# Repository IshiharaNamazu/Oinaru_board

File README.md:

# Oinaru Board

Oinaru Boardは、USB Type-Cからセンサへ電源を供給しながら、PCとセンサ間のUSB–RS485通信を行うための変換基板です。

USB Type-Cから入力された電圧は、XC9306昇降圧DC-DCコンバータモジュールで5 Vに安定化してセンサへ供給します。

USB–UART変換にはCH340E、差動信号の送受信には2個のMAX485Eを使用し、TX±／RX±による4線式通信に対応しています。

## 特長

- USB Type-C（USB 2.0）接続
- センサへの5 V電源供給
- XC9306モジュールによるUSB入力電圧の昇降圧・安定化
- USB–RS485変換
- TX±／RX±の4線式全二重通信
- USB接続および5 V電源のLED表示
- 通信線の終端抵抗を実装可能

## 基板外観

### 表面

### 裏面

## センサ側コネクタ（XH）

| ピン | 信号 |
| ---: | :--- |
| 1 | GND |
| 2 | +5 V |
| 3 | TX+ |
| 4 | TX- |
| 5 | RX+ |
| 6 | RX- |

ピン番号はKiCadの回路図・基板データ上の番号です。実際に接続する前に、使用するセンサの仕様書と信号方向・ピン配列を照合してください。
基盤のTXはセンサのRXと接続されることに注意してください

## 使用方法

1. XHコネクタにセンサを接続します。
2. Oinaru BoardとPCをUSB Type-Cケーブルで接続します。
3. PCに認識されたCH340Eのシリアルポートを、使用するソフトウェアから開きます。
4. センサの仕様に合わせて通信速度などを設定し、通信を開始します。

## 主な構成部品

| 部品 | 用途 |
| :--- | :--- |
| CH340E | USB–UART変換 |
| MAX485E × 2 | TX／RX差動信号変換 |
| XC9306昇降圧モジュール | USB入力電圧を5 Vに安定化 |
| USB Type-Cレセプタクル | PC接続・電源入力 |
| 6ピンコネクタ | センサ接続 |

## オプション部品

以下の部品は必要に応じて実装するオプションです。

- `TRIM_R`：XC9306モジュールの出力電圧調整用抵抗です。使用するモジュールの仕様と必要な出力電圧に合わせて抵抗値を選定します。
- `R6`：TX差動信号線の終端抵抗です。必要に応じて実装します。
- `R7`：RX差動信号線の終端抵抗です。必要に応じて実装します。

## 設計データ

- `usb_rs485_adapter.kicad_pro`：KiCadプロジェクト
- `usb_rs485_adapter.kicad_sch`：回路図
- `usb_rs485_adapter.kicad_pcb`：基板レイアウト
- `production/`：製造用出力データ

## 注意事項

- 本基板の通信部と電源部は絶縁されていません。
- センサの消費電流が、接続するUSBポートやケーブルの給電能力を超えないことを確認してください。
- 配線の誤りや極性の取り違えは、基板・センサ・PCの故障につながる可能性があります。
- 使用環境に応じて終端抵抗の値と実装状態を確認してください。

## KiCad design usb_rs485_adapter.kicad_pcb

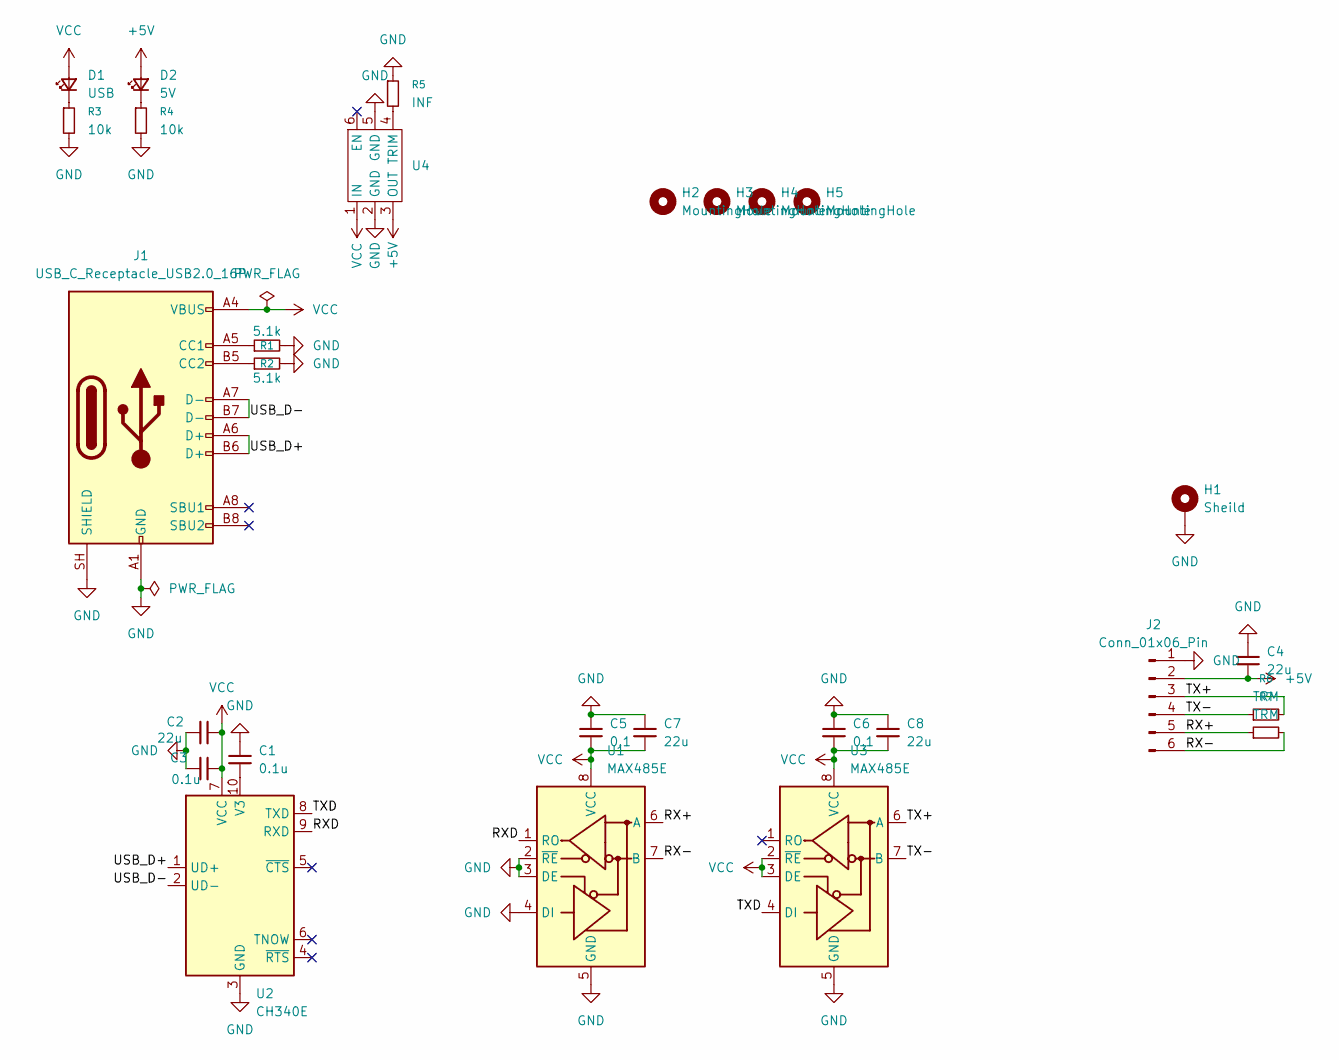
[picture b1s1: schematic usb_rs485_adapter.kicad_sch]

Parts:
C1, C3: 0.1u; C_0603_1608Metric_Pad1.08x0.95mm_HandSolder
C2, C4, C7, C8: 22u; C_0603_1608Metric_Pad1.08x0.95mm_HandSolder
C5, C6: 0.1; C_0603_1608Metric_Pad1.08x0.95mm_HandSolder
D1: USB; LED_0603_1608Metric_Pad1.05x0.95mm_HandSolder
D2: 5V; LED_0603_1608Metric_Pad1.05x0.95mm_HandSolder
H1: Sheild; MountingHole_3.2mm_M3_Pad
H2, H3, H4, H5: MountingHole; MountingHole_3.2mm_M3
J1: USB_C_Receptacle_USB2.0_16P; USB_C_Receptacle_GCT_USB4105-xx-A_16P_TopMnt_Horizontal
J2: Conn_01x06_Pin; JST_XH_S6B-XH-A_1x06_P2.50mm_Horizontal
R1, R2: 5.1k; R_0603_1608Metric_Pad0.98x0.95mm_HandSolder
R3, R4: 10k; R_0603_1608Metric_Pad0.98x0.95mm_HandSolder
R5: INF; R_0603_1608Metric_Pad0.98x0.95mm_HandSolder
R6, R7: TRM; R_0603_1608Metric_Pad0.98x0.95mm_HandSolder
U1, U3: MAX485E; SOIC-8_3.9x4.9mm_P1.27mm
U2: CH340E; MSOP-10_3x3mm_P0.5mm
U4: AE-XC9306-5V0

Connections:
+5V: C4.1, D2.2 (A), J2.2, U4.3 (OUT)
/RX+: J2.5, R7.1, U1.6 (A)
/RX-: J2.6, R7.2, U1.7 (B)
/RXD: U1.1 (RO), U2.9 (RXD)
/TX+: J2.3, R6.2, U3.6 (A)
/TX-: J2.4, R6.1, U3.7 (B)
/TXD: U2.8 (TXD), U3.4 (DI)
/USB_D+: J1.A6 (D+), J1.B6 (D+), U2.1 (UD+)
/USB_D-: J1.A7 (D-), J1.B7 (D-), U2.2 (UD-)
GND: C1.1, C2.1, C3.1, C4.2, C5.2, C6.1, C7.1, C8.1, H1.1 (1_1), J1.A1 (GND), J1.A12 (GND), J1.B1 (GND), J1.B12 (GND), J1.SH (SHIELD), J2.1, R1.2, R2.2, R3.2, R4.2, R5.1, U1.2 (~RE), U1.3 (DE), U1.4 (DI), U1.5 (GND), U2.3 (GND), U3.5 (GND), U4.2 (GND), U4.5 (GND)
unnamed: D1.1 (K), R3.1
unnamed: D2.1 (K), R4.1
unnamed: J1.A5 (CC1), R1.1
unnamed: J1.B5 (CC2), R2.1
unnamed: C1.2, U2.10 (V3)
unnamed: R5.2, U4.4 (TRIM)
VCC: C2.2, C3.2, C5.1, C6.2, C7.2, C8.2, D1.2 (A), J1.A4 (VBUS), J1.A9 (VBUS), J1.B4 (VBUS), J1.B9 (VBUS), U1.8 (VCC), U2.7 (VCC), U3.2 (~RE), U3.3 (DE), U3.8 (VCC), U4.1 (IN)

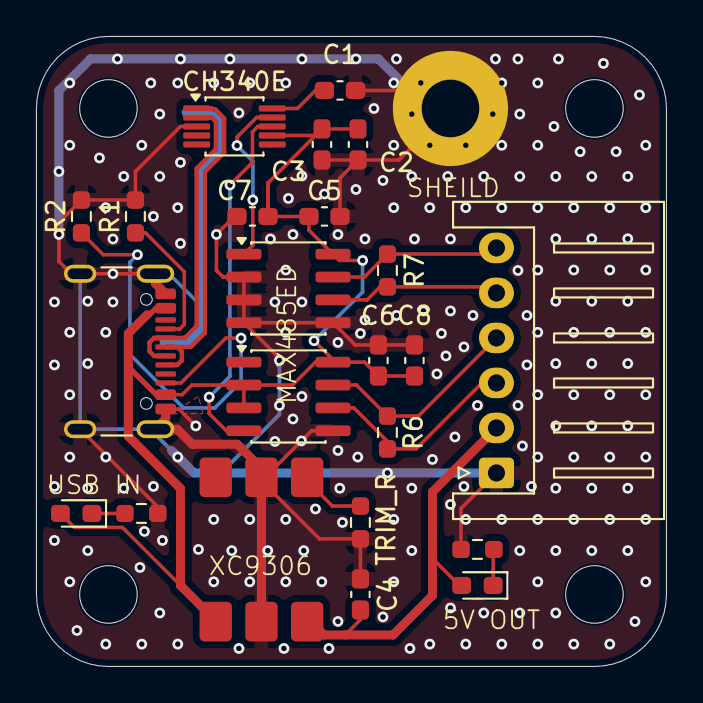
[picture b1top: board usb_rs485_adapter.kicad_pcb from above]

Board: 2 copper layers, 35.0 x 35.0 mm, 28 parts (0 on the bottom side), 17 nets.

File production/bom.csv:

Designator,Footprint,Quantity,Value,LCSC Part #
"C1, C3",0603,2,0.1u,
"C2, C4, C7, C8",0603,4,22u,
"C5, C6",0603,2,0.1,
D1,0603,1,USB,
D2,0603,1,5V,
J1,USB_C_Receptacle_GCT_USB4105-xx-A_16P_TopMnt_Horizontal,1,USB_C_Receptacle_USB2.0_16P,
J2,JST_XH_S6B-XH-A_1x06_P2.50mm_Horizontal,1,Conn_01x06_Pin,
"R1, R2",0603,2,5.1k,
"R3, R4",0603,2,10k,
R5,0603,1,INF,
"R6, R7",0603,2,TRM,
"U1, U3",SOIC-8_3.9x4.9mm_P1.27mm,2,MAX485E,
U2,MSOP-10_3x3mm_P0.5mm,1,CH340E,
U4,AE-XC9306-5V0,1,~,
